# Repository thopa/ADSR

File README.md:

# ADSR
Euroack ADSR envelope generator based on https://gist.github.com/m0xpd
Added LED as visual feedback for the envelope
14hp 30ma @ +12v

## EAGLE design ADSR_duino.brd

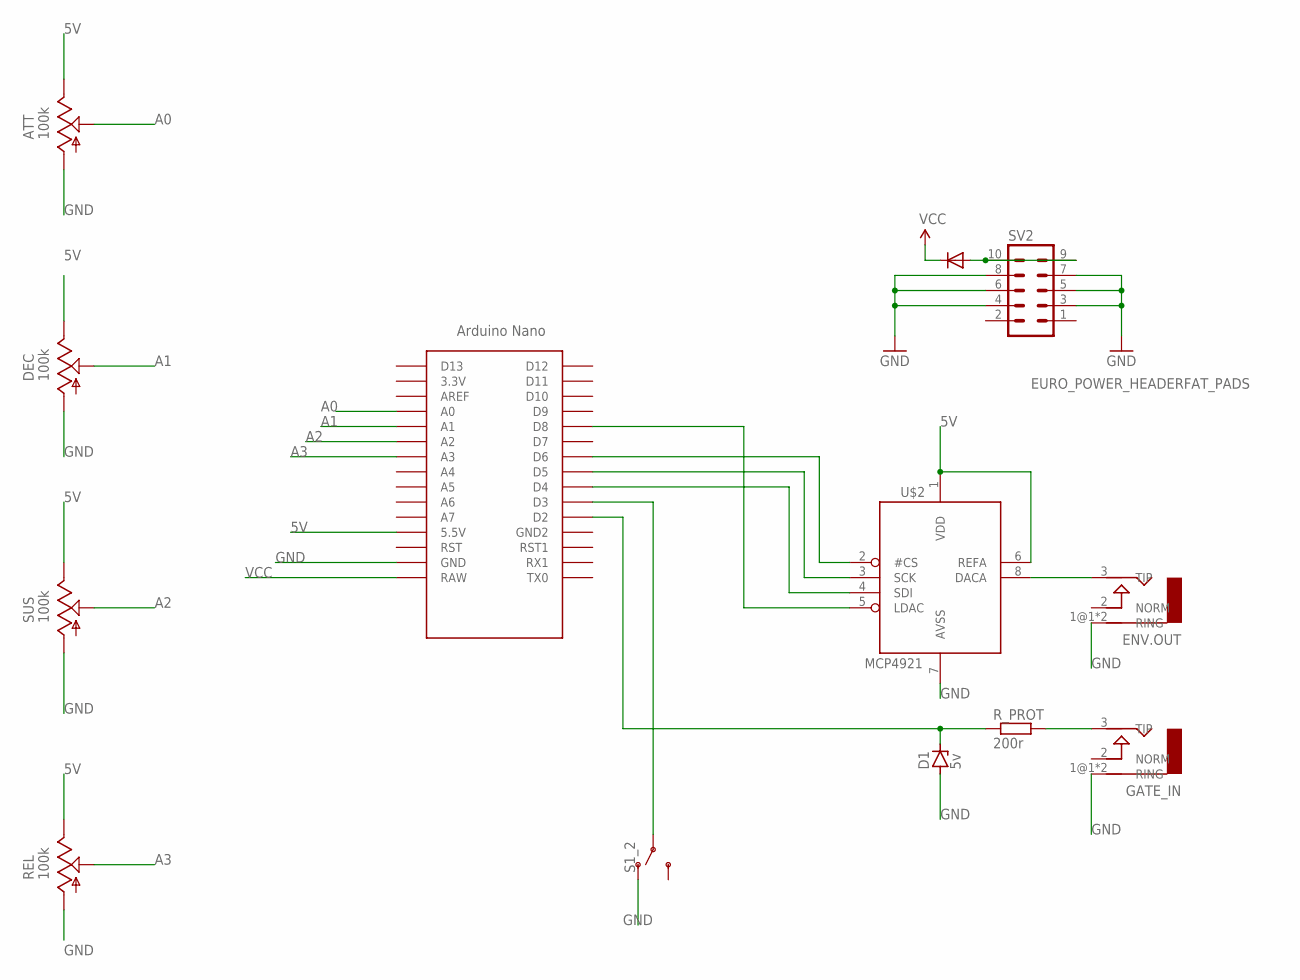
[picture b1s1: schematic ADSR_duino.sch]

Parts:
ATT: 100k; SLIDEPOT-45
D1: 5v; ZDIO-5
D2: 1N5819HW; DO-1N4148
DEC: 100k; SLIDEPOT-45
ENV.OUT: AUDIO-JACKERTHENVAR; ERTHENVAR-JACK
GATE_IN: AUDIO-JACKERTHENVAR; ERTHENVAR-JACK
REL: 100k; SLIDEPOT-45
R_PROT: 200r; 7MM_RESISTOR
S1_2: SWITCH-SPDT-PTH-11.6X4.0MM; SWITCH_SPDT_PTH_11.6X4.0MM
SUS: 100k; SLIDEPOT-45
SV2: EURO_POWER_HEADERFAT_PADS; EURO_PWR_HEADER_FAT
U$1: NANO
U$2: MCP4921; DIL08

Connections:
5V: ATT.B, DEC.B, REL.B, SUS.B, U$1.5V (5.5V), U$2.1 (VDD), U$2.6 (REFA)
A0: ATT.WIPER, U$1.A0
A1: DEC.WIPER, U$1.A1
A2: SUS.WIPER, U$1.A2
A3: REL.WIPER, U$1.A3
GND: ATT.A, D1.A, DEC.A, ENV.OUT.1@1 (RING), ENV.OUT.1@2 (RING), GATE_IN.1@1 (RING), GATE_IN.1@2 (RING), REL.A, S1_2.1 (O), SUS.A, SV2.3, SV2.4, SV2.5, SV2.6, SV2.7, SV2.8, U$1.GND, U$2.7 (AVSS)
unnamed: D2.A, SV2.9, SV2.10
unnamed: S1_2.2, U$1.D3
unnamed: GATE_IN.3 (TIP), R_PROT.2
unnamed: ENV.OUT.3 (TIP), U$2.8 (DACA)
unnamed: D1.C, R_PROT.1, U$1.D2
unnamed: U$1.D4, U$2.4 (SDI)
unnamed: U$1.D5, U$2.3 (SCK)
unnamed: U$1.D6, U$2.2 (#CS)
unnamed: U$1.D8, U$2.5 (LDAC)
VCC: D2.C, U$1.RAW

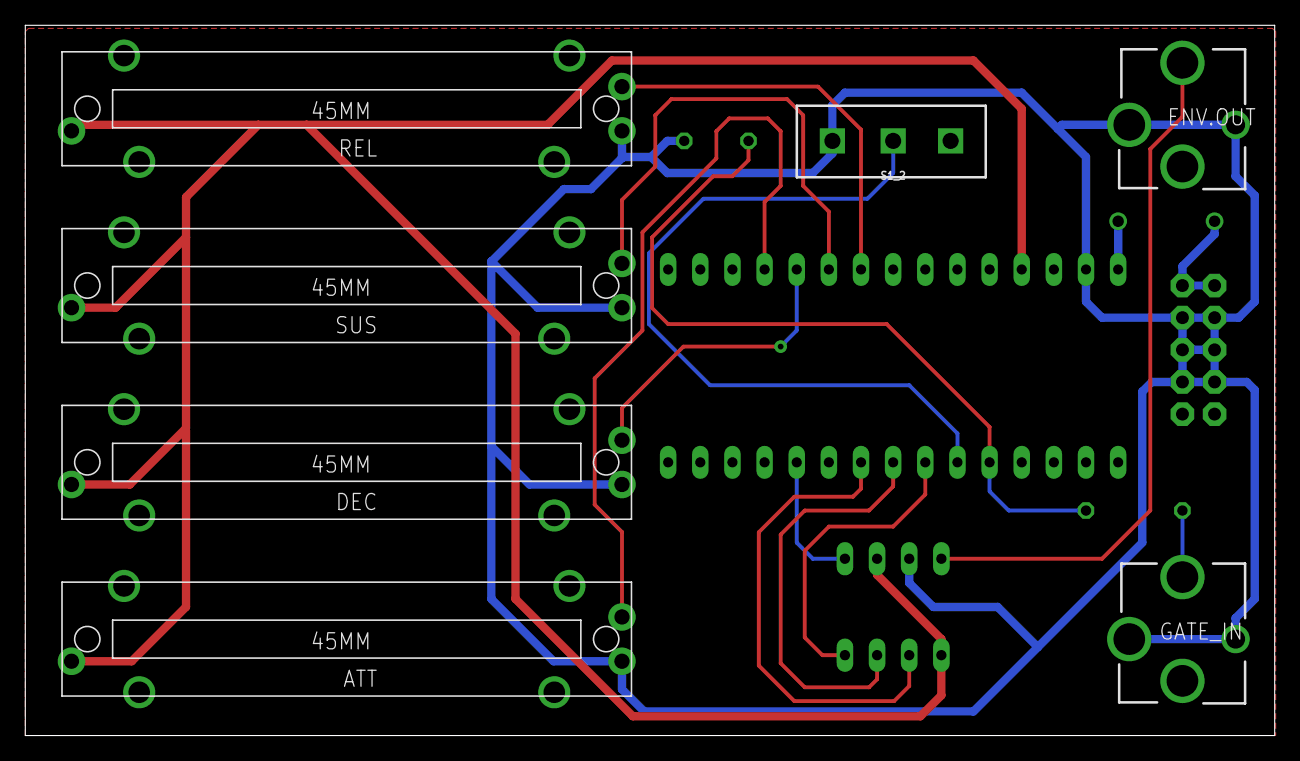
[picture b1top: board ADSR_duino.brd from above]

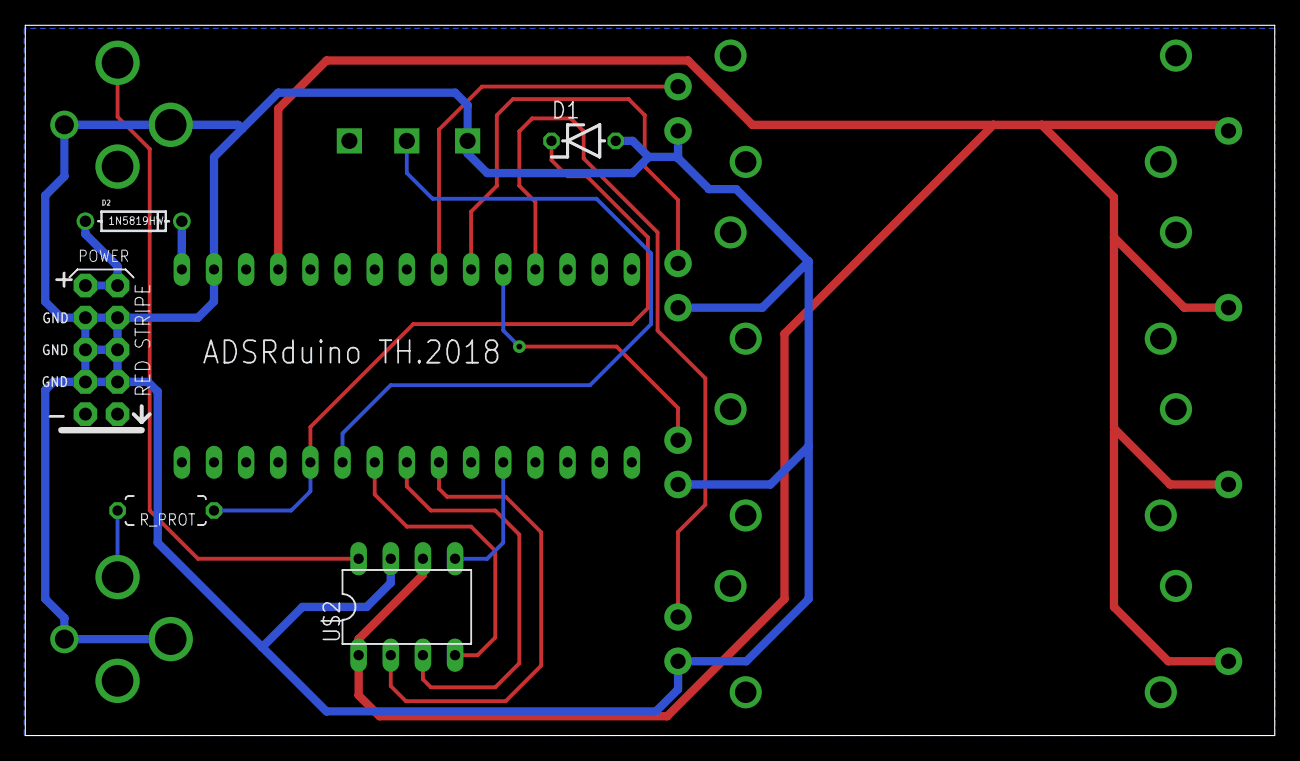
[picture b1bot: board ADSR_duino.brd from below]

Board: 2 copper layers, 98.7 x 56.1 mm, 13 parts (6 on the bottom side), 16 nets.

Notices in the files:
parts and their libraries:
SPDT_Switches_Thonk: Licensing: Creative Commons ShareAlike 4.0 International - https://creativecommons.org/licenses/by-sa/4.0
